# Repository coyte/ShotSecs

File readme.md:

# ShotSecs
Created a little timer that will keep track of how long power (240v) is applied. Originally developed to measure Espresso shots time, but probably useful for other applications.
The usual warnings about tinkering with 240V AC apply!!!

### Introduction
The original idea was that the logic and PSA would be housed inside the espressomachine, and the 7 segment display would be glued/mounted to the exterior of the machine. Hence they are two separate parts connected by a 10-strand data cable
### Hardware
The hardware consists of a little PCB (Kicad schematic & layout included) that hold a Atmega328p, two transistors and 10 resistors to control the 7-segment display.
On the input side I used some resistors and a optocoupler to detect power applied.
PSU, Atmega, optocoupler, resistors and transistors is mounted on the same PCB (220V and 5 V), intended to be drowned in a resin box when donw.

#### Connections (240Volts)
The timer needs a regular 240V connection to power up the Atmega and display. In addition it needs a connection of the applied power
Connect either P-N-Pd or N-P-Nd on the tree terminal block.
Where   P = phase or live wire from 240V mains
        N = null or neutral wire from 240V mains
        Pd= Phase from device to be measured
        Nd= null from device to be measured

### Software
The software is written in AVR C. It essentially is a timer that runs while power is detected by the optocoupler. The display will 'hold' the last known value if power is stopped. On re-applying the power the timer will restart at 0.

Have fun and be careful.

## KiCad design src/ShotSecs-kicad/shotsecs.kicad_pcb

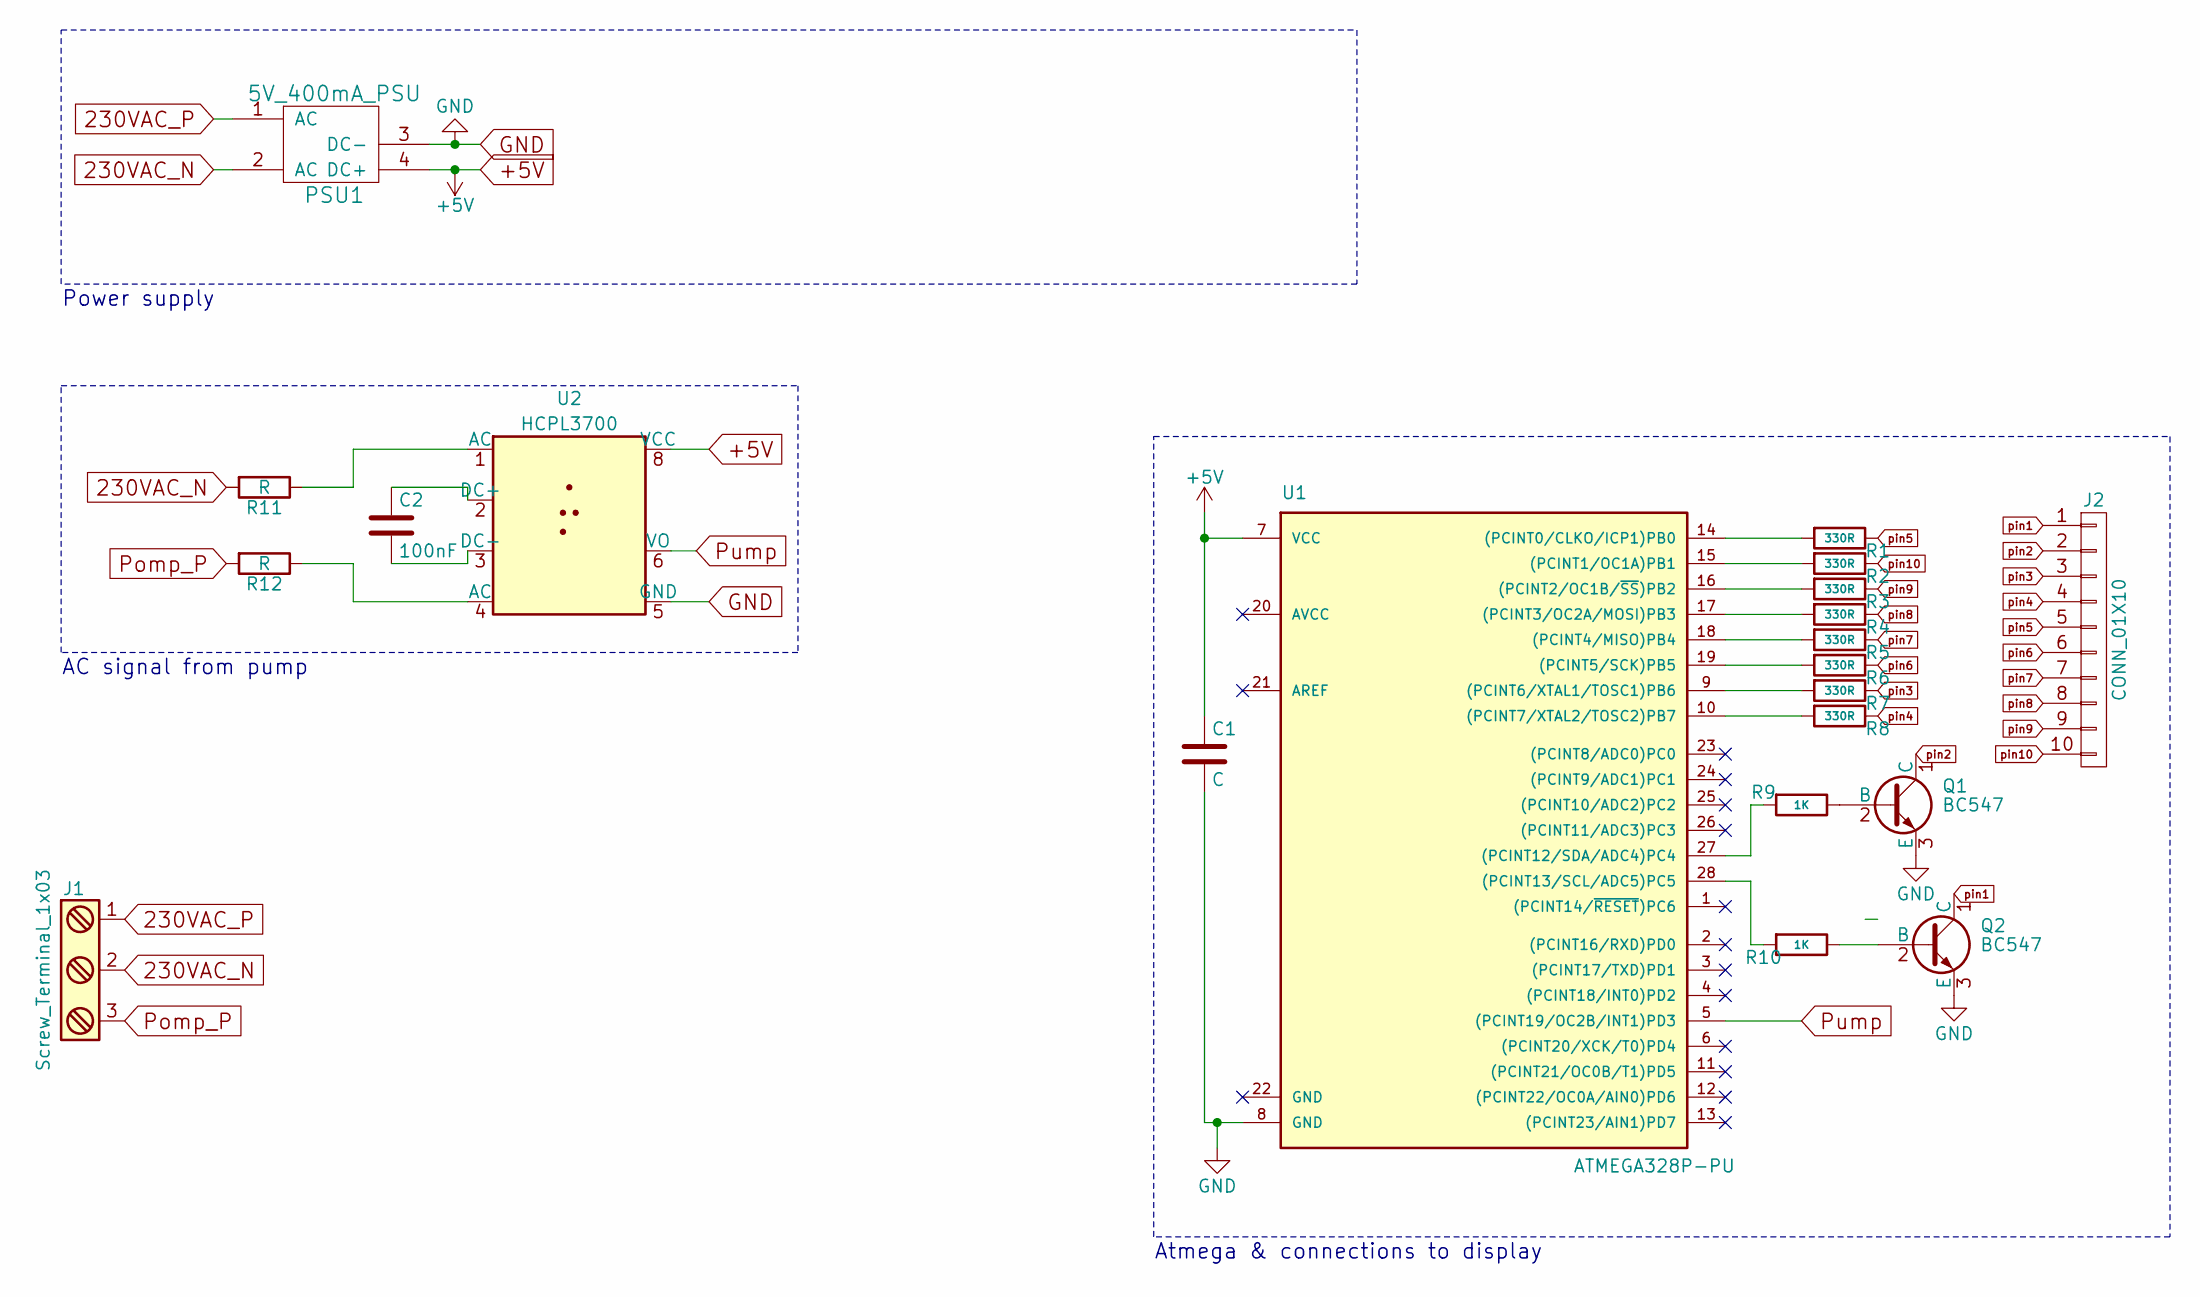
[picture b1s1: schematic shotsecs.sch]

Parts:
C1: C; C_Disc_D3.8mm_W2.6mm_P2.50mm
C2: 100nF; CP_Radial_D8.0mm_P5.00mm
J1: Screw_Terminal_1x03; TerminalBlock_Pheonix_PT-3.5mm_3pol
J2: CONN_01X10; Pin_Header_Straight_1x10_Pitch2.54mm
PSU1: 5V_400mA_PSU; HLK-PM01
Q1, Q2: BC547; TO-92_Molded_Narrow
R1, R2, R3, R4, R5, R6, R7, R8: 330R; R_Axial_DIN0207_L6.3mm_D2.5mm_P7.62mm_Horizontal
R9, R10: 1K; R_Axial_DIN0207_L6.3mm_D2.5mm_P7.62mm_Horizontal
R11, R12: R; R_Axial_DIN0207_L6.3mm_D2.5mm_P7.62mm_Horizontal
U1: ATMEGA328P-PU; DIP-28_W7.62mm
U2: HCPL3700; DIP-8_W7.62mm

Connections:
230VAC_N: J1.2, PSU1.2 (AC), R11.2
230VAC_P: J1.1, PSU1.1 (AC)
+5V: C1.1, PSU1.4 (DC+), U1.7 (VCC), U2.8 (VCC)
GND: C1.2, PSU1.3 (DC-), Q1.3 (E), Q2.3 (E), U1.8 (GND), U2.5 (GND)
unnamed: C2.1, U2.2 (DC+)
unnamed: C2.2, U2.3 (DC-)
unnamed: Q1.2 (B), R9.1
unnamed: Q2.2 (B), R10.1
unnamed: R1.2, U1.14 ((PCINT0/CLKO/ICP1)PB0)
unnamed: R2.2, U1.15 ((PCINT1/OC1A)PB1)
unnamed: R3.2, U1.16 ((PCINT2/OC1B/~SS~)PB2)
unnamed: R4.2, U1.17 ((PCINT3/OC2A/MOSI)PB3)
unnamed: R5.2, U1.18 ((PCINT4/MISO)PB4)
unnamed: R6.2, U1.19 ((PCINT5/SCK)PB5)
unnamed: R7.2, U1.9 ((PCINT6/XTAL1/TOSC1)PB6)
unnamed: R8.2, U1.10 ((PCINT7/XTAL2/TOSC2)PB7)
unnamed: R9.2, U1.27 ((PCINT12/SDA/ADC4)PC4)
unnamed: R10.2, U1.28 ((PCINT13/SCL/ADC5)PC5)
unnamed: R11.1, U2.1 (AC)
unnamed: R12.1, U2.4 (AC)
Pomp_P: J1.3, R12.2
Pump: U1.5 ((PCINT19/OC2B/INT1)PD3), U2.6 (VO)
pin1: J2.1, Q2.1 (C)
pin2: J2.2, Q1.1 (C)
pin3: J2.3, R7.1
pin4: J2.4, R8.1
pin5: J2.5, R1.1
pin6: J2.6, R6.1
pin7: J2.7, R5.1
pin8: J2.8, R4.1
pin9: J2.9, R3.1
pin10: J2.10, R2.1

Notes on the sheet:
Power supply
AC signal from pump
Atmega & connections to display

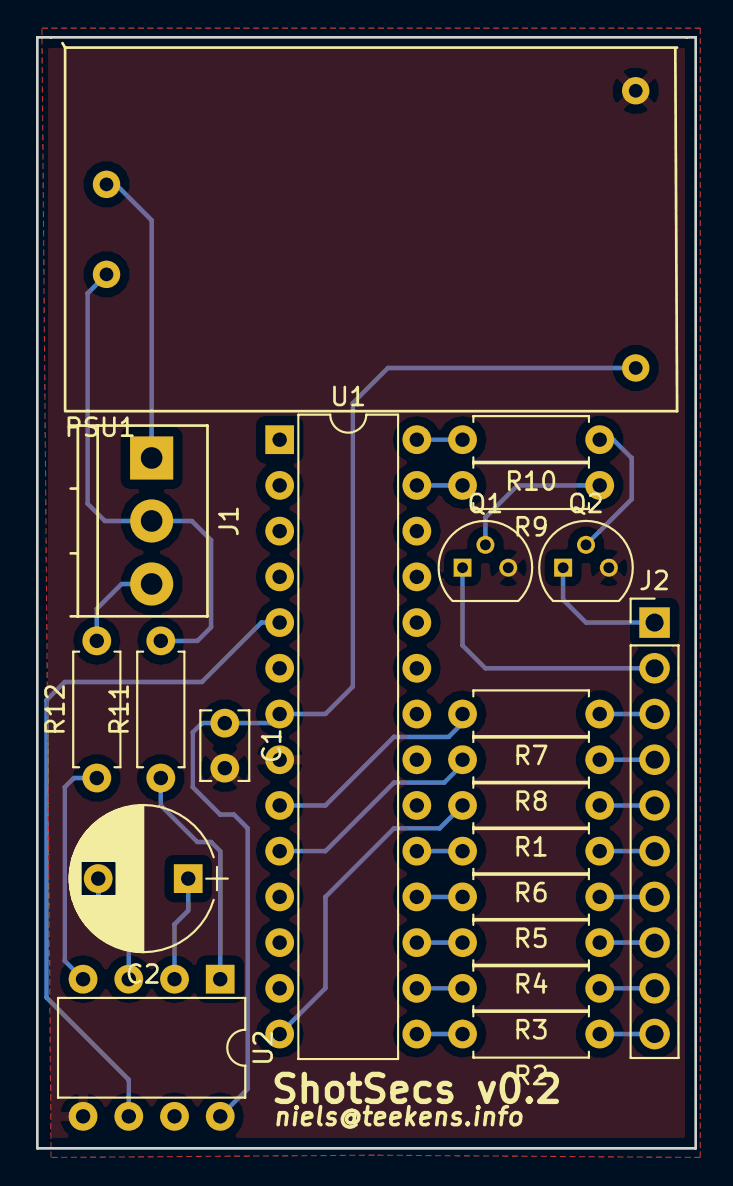
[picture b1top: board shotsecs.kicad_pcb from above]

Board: 2 copper layers, 36.6 x 61.7 mm, 21 parts (0 on the bottom side), 32 nets.
